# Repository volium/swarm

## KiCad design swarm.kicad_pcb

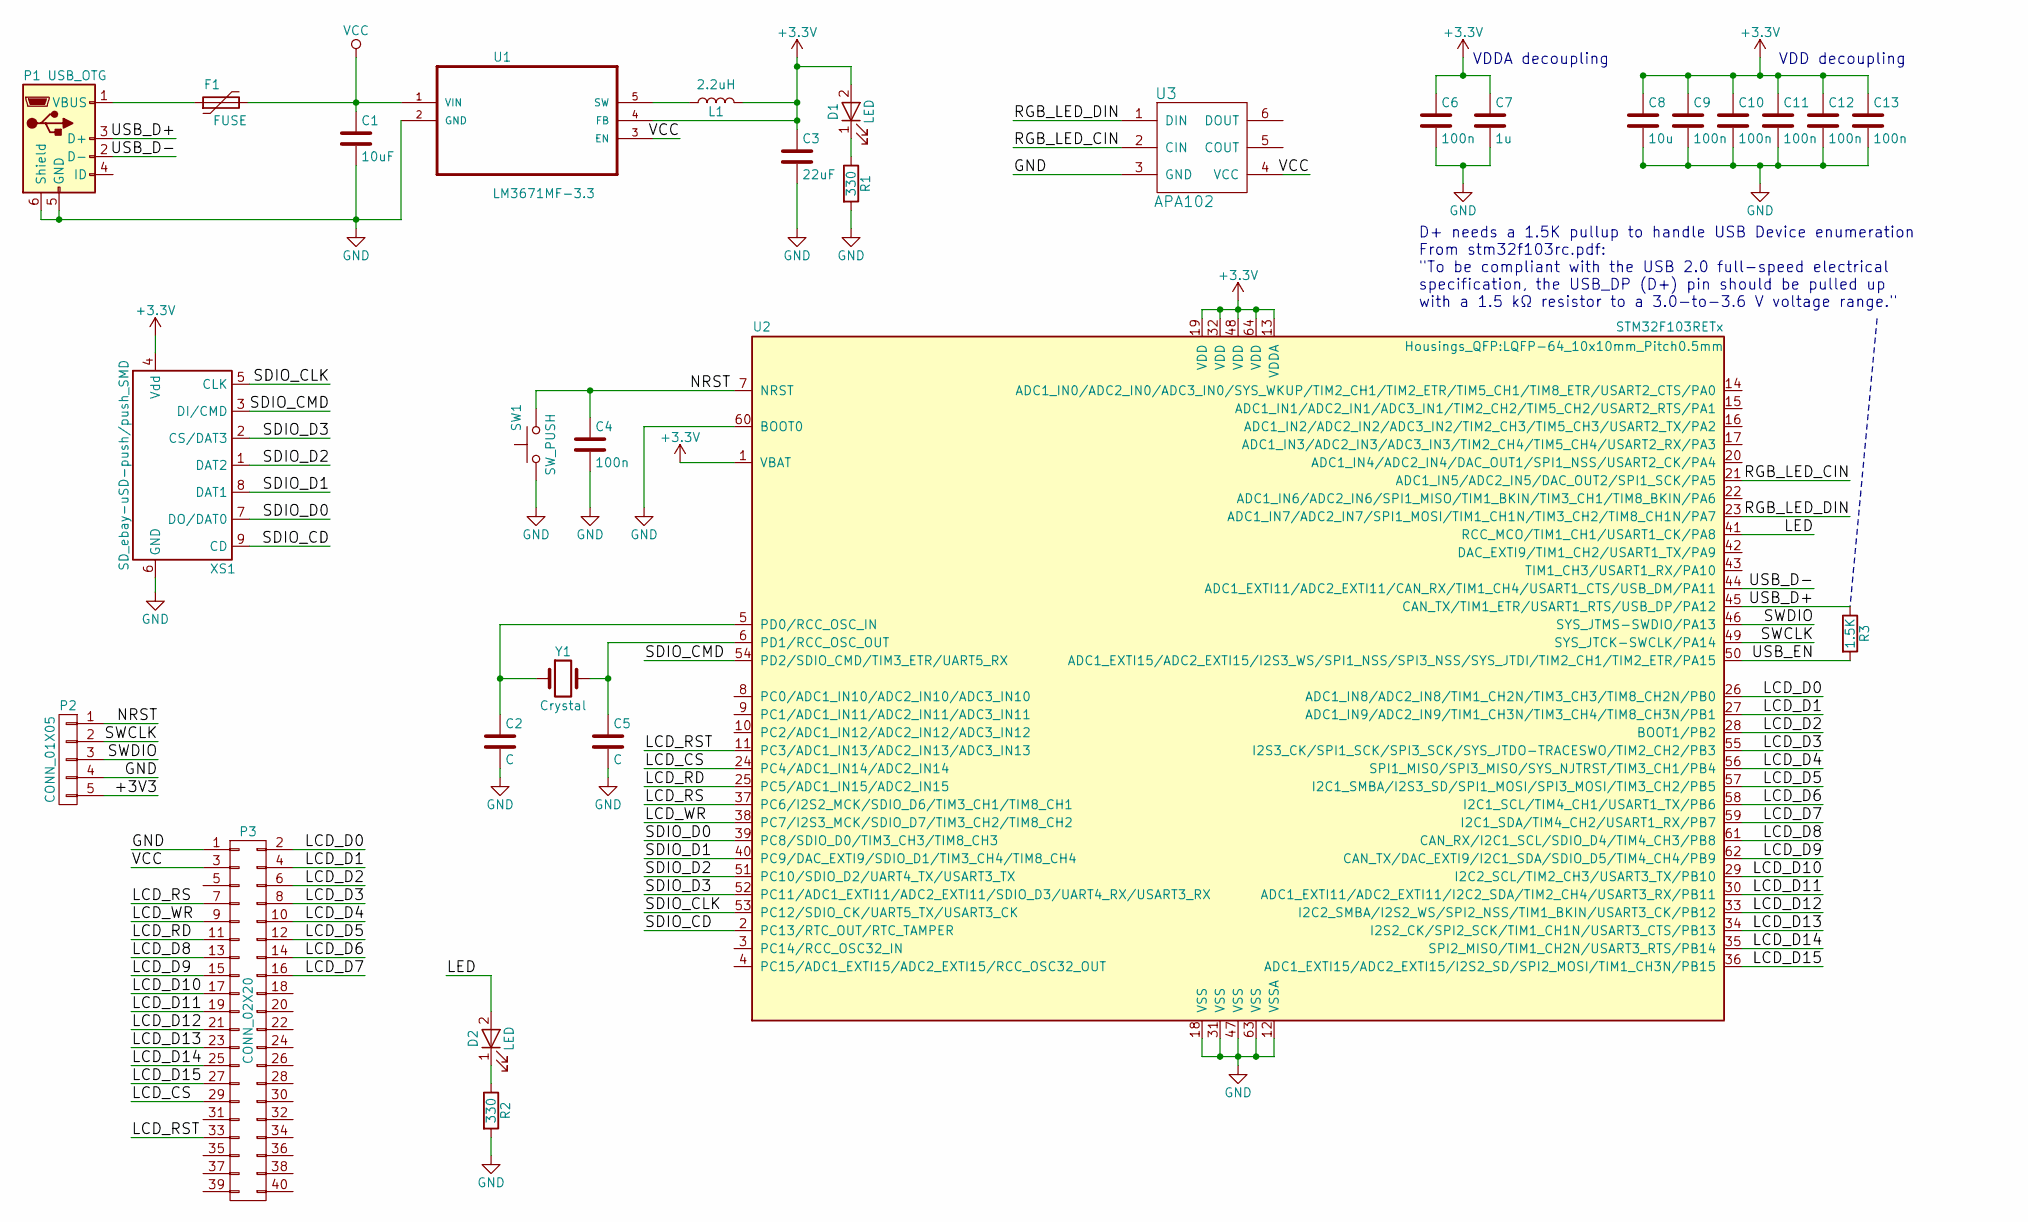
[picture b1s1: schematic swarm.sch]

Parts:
C1: 10uF; C_0805
C2, C5: C; C_0805
C3: 22uF; C_0805
C4, C6, C9, C10, C11, C12, C13: 100n; C_0805
C7: 1u; C_0805
C8: 10u; C_0805
D1, D2: LED; LED_0805
F1: FUSE; MF-PSMF050X
L1: 2.2uH; Inductor_Taiyo-Yuden_NR-24xx_HandSoldering
P1: USB_OTG; USB_Mini-B
P2: CONN_01X05; Pin_Header_Angled_1x05
P3: CONN_02X20; Pin_Header_Straight_2x20
R1, R2: 330; R_0805
R3: 1.5K; R_0805
SW1: SW_PUSH; SW_SPST_PTS645
U1: LM3671MF-3.3; SOT-23-5
U2: STM32F103RETx; LQFP-64_10x10mm_Pitch0.5mm
U3: APA102
XS1: SD_ebay-uSD-push/push_SMD; Conn_uSDcard
Y1: Crystal; Crystal_SMD_5032_2Pads

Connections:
/LCD_CS: P3.29, U2.24 (PC4/ADC1_IN14/ADC2_IN14)
/LCD_D0: P3.2, U2.26 (ADC1_IN8/ADC2_IN8/TIM1_CH2N/TIM3_CH3/TI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)
/LCD_D1: P3.4, U2.27 (ADC1_IN9/ADC2_IN9/TIM1_CH3N/TIM3_CH4/TI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)
/LCD_D2: P3.6, U2.28 (BOOT1/PB2)
/LCD_D3: P3.8, U2.55 (I2S3_CK/SPI1_SCK/SPI3_SCK/SYS_JTDO-TRAC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)
/LCD_D4: P3.10, U2.56 (SPI1_MISO/SPI3_MISO/SYS_NJTRST/TIM3_CH1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)
/LCD_D5: P3.12, U2.57 (I2C1_SMBA/I2S3_SD/SPI1_MOSI/SPI3_MOSI/T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)
/LCD_D6: P3.14, U2.58 (I2C1_SCL/TIM4_CH1/USART1_TX/PB6)
/LCD_D7: P3.16, U2.59 (I2C1_SDA/TIM4_CH2/USART1_RX/PB7)
/LCD_D8: P3.13, U2.61 (CAN_RX/I2C1_SCL/SDIO_D4/TIM4_CH3/PB8)
/LCD_D9: P3.15, U2.62 (CAN_TX/DAC_EXTI9/I2C1_SDA/SDIO_D5/TIM4_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)
/LCD_D10: P3.17, U2.29 (I2C2_SCL/TIM2_CH3/USART3_TX/PB10)
/LCD_D11: P3.19, U2.30 (ADC1_EXTI11/ADC2_EXTI11/I2C2_SDA/TIM2_C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)
/LCD_D12: P3.21, U2.33 (I2C2_SMBA/I2S2_WS/SPI2_NSS/TIM1_BKIN/US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)
/LCD_D13: P3.23, U2.34 (I2S2_CK/SPI2_SCK/TIM1_CH1N/USART3_CTS/P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)
/LCD_D14: P3.25, U2.35 (SPI2_MISO/TIM1_CH2N/USART3_RTS/PB14)
/LCD_D15: P3.27, U2.36 (ADC1_EXTI15/ADC2_EXTI15/I2S2_SD/SPI2_MO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)
/LCD_RD: P3.11, U2.25 (PC5/ADC1_IN15/ADC2_IN15)
/LCD_RS: P3.7, U2.37 (PC6/I2S2_MCK/SDIO_D6/TIM3_CH1/TIM8_CH1)
/LCD_RST: P3.33, U2.11 (PC3/ADC1_IN13/ADC2_IN13/ADC3_IN13)
/LCD_WR: P3.9, U2.38 (PC7/I2S3_MCK/SDIO_D7/TIM3_CH2/TIM8_CH2)
/LED: D2.2 (A), U2.41 (RCC_MCO/TIM1_CH1/USART1_CK/PA8)
/NRST: C4.1, P2.1, SW1.2, U2.7 (NRST)
/RGB_LED_CIN: U2.21 (ADC1_IN5/ADC2_IN5/DAC_OUT2/SPI1_SCK/PA5), U3.2 (CIN)
/RGB_LED_DIN: U2.23 (ADC1_IN7/ADC2_IN7/SPI1_MOSI/TIM1_CH1N/T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), U3.1 (DIN)
/SDIO_CD: U2.2 (PC13/RTC_OUT/RTC_TAMPER), XS1.9 (CD)
/SDIO_CLK: U2.53 (PC12/SDIO_CK/UART5_TX/USART3_CK), XS1.5 (CLK)
/SDIO_CMD: U2.54 (PD2/SDIO_CMD/TIM3_ETR/UART5_RX), XS1.3 (DI/CMD)
/SDIO_D0: U2.39 (PC8/SDIO_D0/TIM3_CH3/TIM8_CH3), XS1.7 (DO/DAT0)
/SDIO_D1: U2.40 (PC9/DAC_EXTI9/SDIO_D1/TIM3_CH4/TIM8_CH4), XS1.8 (DAT1)
/SDIO_D2: U2.51 (PC10/SDIO_D2/UART4_TX/USART3_TX), XS1.1 (DAT2)
/SDIO_D3: U2.52 (PC11/ADC1_EXTI11/ADC2_EXTI11/SDIO_D3/UA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), XS1.2 (CS/DAT3)
/SWCLK: P2.2, U2.49 (SYS_JTCK-SWCLK/PA14)
/SWDIO: P2.3, U2.46 (SYS_JTMS-SWDIO/PA13)
/USB_D+: P1.3 (D+), R3.1, U2.45 (CAN_TX/TIM1_ETR/USART1_RTS/USB_DP/PA12)
/USB_D-: P1.2 (D-), U2.44 (ADC1_EXTI11/ADC2_EXTI11/CAN_RX/TIM1_CH4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)
/USB_EN: R3.2, U2.50 (ADC1_EXTI15/ADC2_EXTI15/I2S3_WS/SPI1_NS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)
GND: C1.2, C2.2, C3.2, C4.2, C5.2, C6.2, C7.2, C8.2, C9.2, C10.2, C11.2, C12.2, C13.2, P1.5 (GND), P1.6 (Shield), P2.4, P3.1, R1.2, R2.2, SW1.1, U1.2 (GND), U2.12 (VSSA), U2.18 (VSS), U2.31 (VSS), U2.47 (VSS), U2.60 (BOOT0), U2.63 (VSS), U3.3 (GND), XS1.6 (GND)
unnamed: C2.1, U2.5 (PD0/RCC_OSC_IN), Y1.1
unnamed: C5.1, U2.6 (PD1/RCC_OSC_OUT), Y1.2
unnamed: D1.1 (K), R1.1
unnamed: D2.1 (K), R2.1
unnamed: F1.1, P1.1 (VBUS)
unnamed: L1.1, U1.5 (SW)
VCC: C1.1, F1.2, P3.3, U1.1 (VIN), U1.3 (EN), U3.4 (VCC)

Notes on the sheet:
VDDA decoupling
VDD decoupling
D+ needs a 1.5K pullup to handle USB Device enumeration From stm32f103rc.pdf: "To be compliant with the USB 2.0 full-speed electrical specification, the USB_DP (D+) pin should be pulled up with a 1.5 kΩ resistor to a 3.0-to-3.6 V voltage range."

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
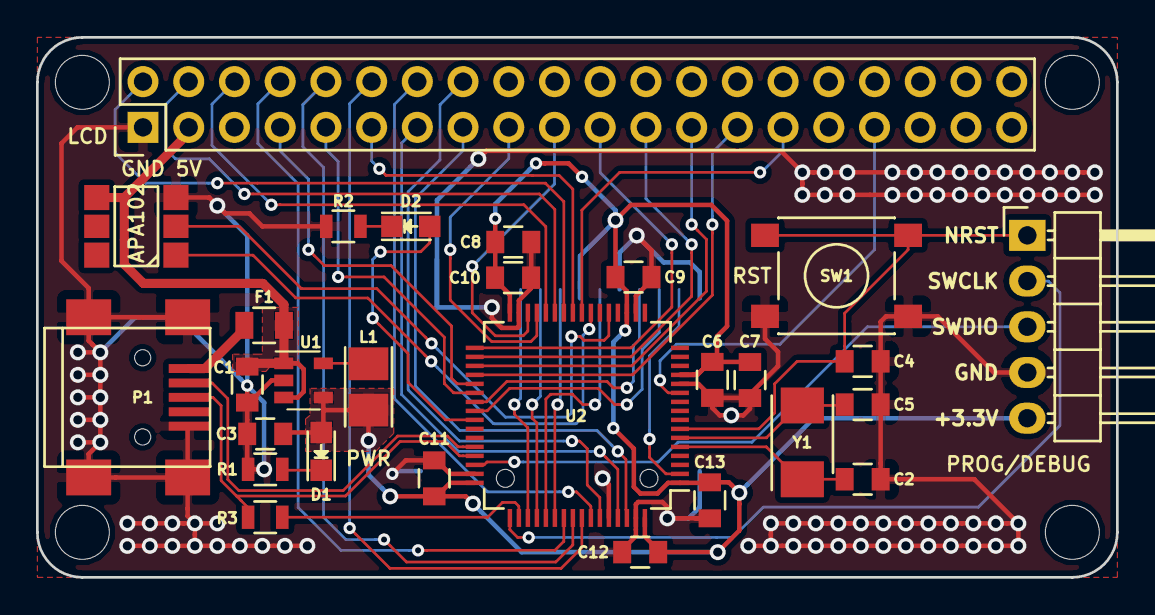
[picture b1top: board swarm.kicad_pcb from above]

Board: 2 copper layers, 60.0 x 30.0 mm, 29 parts (0 on the bottom side), 46 nets.

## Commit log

2016-10-28 First commit, adds STM32F103RE
2016-10-28 Stop tracking backups
2016-10-28 Adds *.bak to .gitignore
2016-10-30 Adds decouplings capacitors
2016-12-01 Adds power sypply based on proven LM3671MF-3.3
2016-12-01 Updates netlist, footprint selection
2016-12-02 Adds MicroSD card and Mini USB connector via volium KiCad library
2016-12-03 Adds Micro SD card socket connection
2016-12-03 Adds LCD connector 2x20 pins
2016-12-04 Adds Serial Wire Debug connector (5 pins) Sets up PCB layers based on Osh Park's Layer setup
2016-12-04 Updates to Design Rules and board thicknes based on Osh Park's setup
2016-12-04 Replaces 0603 components with smaller fooprint Regenerated net file and imported in pcbnew
2016-12-04 Adds APA102 SPI RGB LED Updates schematic references and links docoupling capacitors based on input pin
2016-12-04 Adds U3 (APA102 LED) to pcbnew
2016-12-06 Moves some components around, no significant changes
2016-12-07 Moving towards routing Switched to 0805 components Locked connectors and MCU, routed part of LCD_DBXX signals
2016-12-07 Lots of nets routed
2016-12-08 Further along in routing, doing well
2016-12-08 All LCD DBXX signals routed
2016-12-08 All LCD signal routed, still lots of cleanup
2016-12-08 Resaved after more routing
2016-12-08 Fixes issue with GND and Vdd swapped for micro SD connector
2016-12-08 Routed all LCD-related signals
2016-12-08 Connected USB (D+, D-) signals (routable)
2016-12-08 Routed all LCD signals (not LCD_DB9), and capacitos, only power supply left
2016-12-08 Routed all LCD signals
2016-12-08 Added SDIO_CD (Card Detect) pin MCU, routed
2016-12-08 Fully routed, no DRC errors
2016-12-09 Fixed DRC violations after adding 'Power' net constraints
2016-12-09 Fixed crooked wire
2016-12-09 Sime very important changes Connect LCD_VCC pin to VCC net, this was previously not connected Makes all elements (tracks and vias) in Power net compliant with its constraints
2016-12-09 Fixes track width
2016-12-09 More cleanup
2016-12-09 Connected missing ground pad, DRC back at 0 errors, added some vias
2016-12-10 Improvements and cleanup Via stitching, moved Debug (P2) connector to the right
2016-12-10 More via stitching
2016-12-10 Swapped physical locations of push button and APA102
2016-12-10 All signals routed, including APA102 CLK, DATA More via cleanup
2016-12-10 Saved after merge, no real changes
2016-12-10 Removes unnecessary track on bottom (NRST)
2016-12-12 Adds fuse (MF-PSMF050X) to schematic and layout
2016-12-12 Updates footprints, adds via to connect ground to APA102
2016-12-12 Via stitching
2016-12-12 Fixes pinout of debug connector, still needs to reroute
2016-12-12 More changes Finished routing debug connector Added labels to debug connector pins
2016-12-14 Cleanup Added back 3D model for L1 inductor (lost in a previous commit) More via stitching
2016-12-14 More cleanup Moved some tracks, reran DRC
2016-12-14 Major cleanup Resized references to 0.6 width and height Increased width of VCC track
2016-12-15 Added new copper zone for +3.3V around power supply components
2016-12-19 Adds LED to TIM2_CH1 (pin 50) Added PWR label, cleanup
2016-12-23 Updates after upgrading to KiCAD 4.0.5 Updated schematic components to new libraries Cleaned up some tracks in layout
2016-12-23 Minor changes
2016-12-23 Moved some vias, cleaned up some tracks
2016-12-23 Fixed "no_connects", cleaned up some tracks
2016-12-26 Decreased clearance to 12 mils for GND planes (top and bottom)
2016-12-27 Added copper zone for VCC Cleaned up silk screen layer
2016-12-27 Moved via to fix remaining DRC issue
2016-12-27 Added OSHW logo (silkscreen)
2016-12-27 Recalculated DRC
2016-12-27 Moved via to allow for better copper fill (GND)
2016-12-27 Adds final gerber files
2017-01-04 Updates kicad_pcb file after re-running "refill all zones" and "DRC"
2017-01-11 Updates 3D model for LCD P3 (2-row 20-pin) connector I had the wrong model for the P3 connector, it was always supposed to be a socket strip (female) connector, not male pins. Adds grid originin at 1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
2017-01-16 Connects 'BOOT0' pin (60) to ground Forgot to connect this pin in Rev 1.0, this pin need to be '0' to select Boot Mode "Main Flash memory" In layout, connected PIN 60 (BOOT0) to GND using 'via'
2017-01-16 Re-ran DRC, no_connects back to 0
2017-01-17 Cosmetic change to schematic, regenerated net file
2017-01-18 Create LICENSE
2017-01-27 Adds USB 1.5K pullup via GPIO Connects 1.5K pullup resistor to D+ of USB, as stated by stm32f103rc.pdf. Connected resistor to PIN PA15 to allow for SW control (USB_EN). Moves LED from pin PA15 to PA8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
2017-01-27 Reran DRC on PCB, no design changes
2017-01-27 Moves SD card connector (Conn_uSDcard) 0.5 mm up Rerouted all necessary signals around Conn_uSDcard drill holes, redid tracks to Conn_uSDcard pads. Cleaned up some tracks and vias. Reran DRC
2017-07-22 Updates project to KiCad 4.0.6 Replaces USB connector schematic symbol, regenerated netlist, updated PCB file
2017-07-30 Updates XS1 Conn_uSDcard footprint with updated component in volium library (updated 3D model)
2017-07-30 Updates U3 APA102 footprint with updated component in volium library (updated 3D model)
2017-07-30 Updates 3D Model for P1 (USB Mini-B) and L1 (Inductor)
    Updated footprint of P1, USB_Mini-B, using updated version of volium library (updated 3D model)
    Updated 3D Model for L1, using new NR2412 model in 3DModels repository
2017-08-13 Updates 3D Model for MF-PSMF020X.wrl
    Updates model with new updated version available in Volium 3D models repository (no scaling, shifting, rotation necessary)
